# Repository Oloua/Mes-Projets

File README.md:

## Présentation

Bienvenue sur mon dépôt 👋

Ce repository regroupe l’ensemble de mes projets académiques, personnels et techniques dans les domaines de l’**intelligence artificielle**, des **systèmes embarqués**, de la **robotique**, de l’**IoT**, de la **vision par ordinateur** et du **développement logiciel**.

L’objectif de ce dépôt est de centraliser mes travaux, de suivre mon évolution en ingénierie et de constituer un **portfolio technique structuré** à destination des collaborateurs.

Les projets présents couvrent notamment :
- 🧠 **Intelligence artificielle / Machine Learning** : classification, apprentissage supervisé et non supervisé, analyse de données
- 🤖 **Robotique & systèmes embarqués** : contrôle de systèmes matériels, bras robotisé, intégration hardware/software
- 📡 **IoT (Internet of Things)** : capteurs, acquisition de données, communication sans fil, systèmes connectés
- 👁️ **Vision par ordinateur** : détection, reconnaissance faciale, traitement d’images
- ⚙️ **Développement logiciel & bas niveau** : Python, C/C++, Rust, MATLAB, OpenCV, TensorFlow
- 🔧 **Électronique & FPGA** : conception de systèmes numériques et prototypage matériel

Chaque dossier correspond à un projet indépendant (ex : *Projet IoT*, *Machine Learning*, *Voiture autonome en FreeRTOS*, *Identification faciale*, *Projet de fin d’études AI-in-Colibry-NPU*, *Stage 2025 Exosquelette*, etc.).

Certains fichiers volumineux (datasets, exécutables, environnements virtuels) sont exclus via `.gitignore` afin de garantir un dépôt propre et léger.

Ce dépôt évolue continuellement avec l’ajout de nouveaux projets et l’amélioration des projets existants.

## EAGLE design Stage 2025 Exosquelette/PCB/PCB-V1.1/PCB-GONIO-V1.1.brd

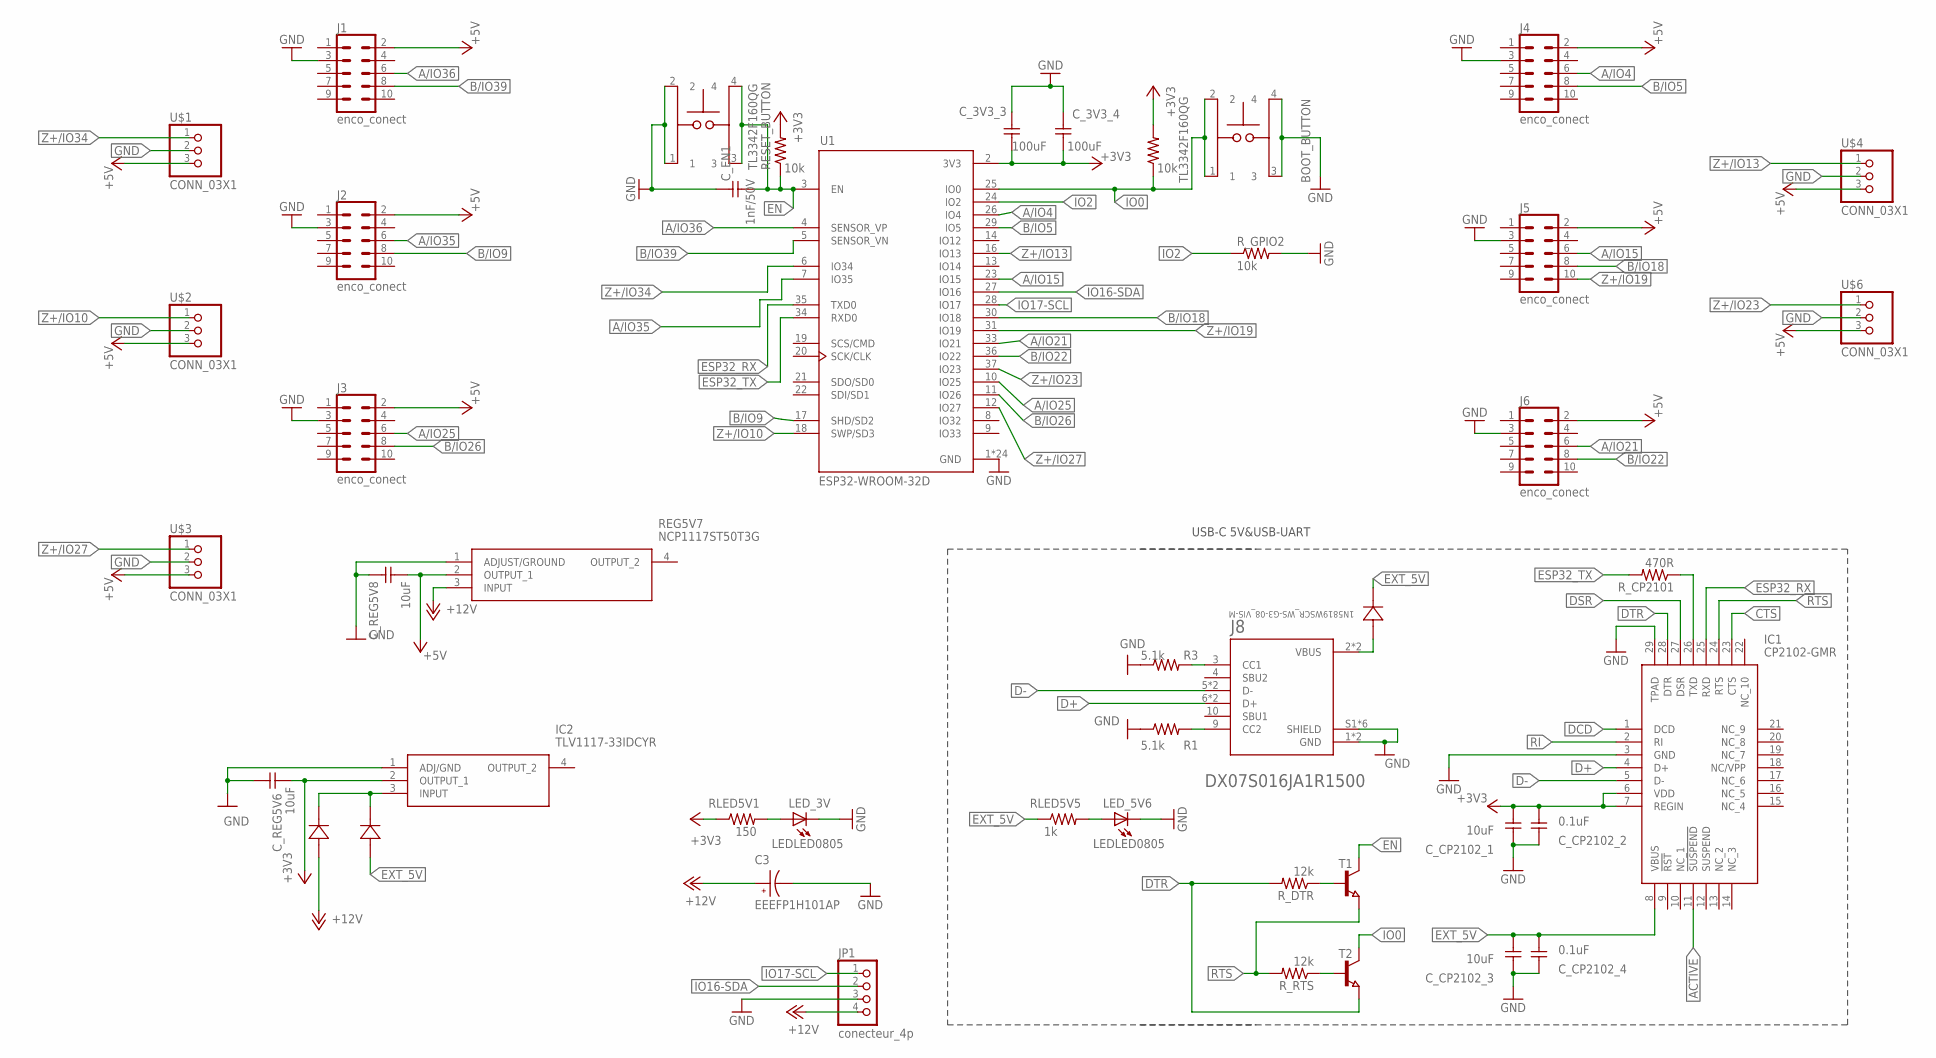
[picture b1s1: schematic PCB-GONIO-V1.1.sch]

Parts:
BOOT_BUTTON: TL3342F160QG; SW_TL3342F160QG
C3: EEEFP1H101AP; CAP_EEEFP1H101AP
CR1, CR2, CR3: 1N5819WSCR_WS-G3-08_VIS-M; CR_WS-G3-08_VIS-M
C_3V3_3, C_3V3_4: 100uF; C1206FAB
C_CP2102_1, C_CP2102_3: 10uF; C1206FAB
C_CP2102_2, C_CP2102_4: 0.1uF; C1206FAB
C_EN1: 1nF/50V; C1206FAB
C_REG5V6, C_REG5V8: 10uF; C1206FAB
IC1: CP2102-GMR; QFN50P500X500X100-29N
IC2: TLV1117-33IDCYR; SOT230P700X180-4N
J1, J2, J3, J4, J5, J6: enco_conect; 2X5-SHROUDED
J8: DX07S016JA1R1500; JAE_DX07S016JA1R1500
JP1: conecteur_4p; 1X04
LED_3V, LED_5V6: LEDLED0805; LEDC2012X90N
R1, R3: 5.1k; R1206W
REG5V7: NCP1117ST50T3G; SOT230P700X180-4N
RESET_BUTTON: TL3342F160QG; SW_TL3342F160QG
RLED5V1: 150; R1206FAB
RLED5V5: 1k; R1206FAB
R_CP2101: 470R; R1206FAB
R_DTR: 12k; R1206FAB
R_GPIO2: 10k; R1206FAB
R_PULL_UP1, R_PULL_UP3: 10k; R1206FAB
R_RTS: 12k; R1206FAB
T1, T2: T_NPN_S8050-J3Y_CHANGJ_SOT23-BEC; SOT23
U1: ESP32-WROOM-32D; MODULE_ESP32-WROOM-32D
U$1, U$2, U$3, U$4, U$6: CONN_03X1; 1X3

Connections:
+3V3: C_3V3_3.1, C_3V3_4.1, C_CP2102_1.1, C_CP2102_2.1, C_REG5V6.1, IC1.6 (VDD), IC1.7 (REGIN), IC2.2 (OUTPUT_1), RLED5V1.1, R_PULL_UP1.2, R_PULL_UP3.2, U1.2 (3V3)
+5V: C_REG5V8.1, J1.2, J2.2, J3.2, J4.2, J5.2, J6.2, REG5V7.2 (OUTPUT_1), U$1.3, U$2.3, U$3.3, U$4.3, U$6.3
+12V: C3.1, CR2.2, JP1.4, REG5V7.3 (INPUT)
A/IO4: J4.6, U1.26 (IO4)
A/IO15: J5.6, U1.23 (IO15)
A/IO21: J6.6, U1.33 (IO21)
A/IO25: J3.6, U1.10 (IO25)
A/IO35: J2.6, U1.7 (IO35)
A/IO36: J1.6, U1.4 (SENSOR_VP)
ACTIVE: IC1.11 (!SUSPEND)
B/IO5: J4.8, U1.29 (IO5)
B/IO9: J2.8, U1.17 (SHD/SD2)
B/IO18: J5.8, U1.30 (IO18)
B/IO22: J6.8, U1.36 (IO22)
B/IO26: J3.8, U1.11 (IO26)
B/IO39: J1.8, U1.5 (SENSOR_VN)
CTS: IC1.23 (CTS)
D+: IC1.4 (D+), J8.6 (D+), J8.7 (D+)
D-: IC1.5 (D-), J8.5 (D-), J8.8 (D-)
DCD: IC1.1 (DCD)
DSR: IC1.27 (DSR)
DTR: IC1.28 (DTR), R_DTR.2, T2.2 (E)
EN: C_EN1.1, RESET_BUTTON.3, RESET_BUTTON.4, R_PULL_UP1.1, T1.3 (C), U1.3 (EN)
ESP32_RX: IC1.25 (RXD), U1.35 (TXD0)
ESP32_TX: R_CP2101.2, U1.34 (RXD0)
EXT_5V: CR1.1, CR3.2, C_CP2102_3.1, C_CP2102_4.1, IC1.8 (VBUS), RLED5V5.1
GND: BOOT_BUTTON.3, BOOT_BUTTON.4, C3.2, C_3V3_3.2, C_3V3_4.2, C_CP2102_1.2, C_CP2102_2.2, C_CP2102_3.2, C_CP2102_4.2, C_EN1.2, C_REG5V6.2, C_REG5V8.2, IC1.3 (GND), IC1.29 (TPAD), IC2.1 (ADJ/GND), J1.3, J2.3, J3.3, J4.3, J5.3, J6.3, J8.1 (GND), J8.12 (GND), J8.S1 (SHIELD), J8.S2 (SHIELD), J8.S3 (SHIELD), J8.S4 (SHIELD), J8.S5 (SHIELD), J8.S6 (SHIELD), JP1.3, LED_3V.1 (C), LED_5V6.1 (C), R1.1, R3.1, REG5V7.1 (ADJUST/GROUND), RESET_BUTTON.1, RESET_BUTTON.2, R_GPIO2.2, U1.1 (GND), U1.15 (GND), U1.38 (GND), U1.39_1 (GND), U1.39_2 (GND), U1.39_3 (GND), U1.39_4 (GND), U1.39_5 (GND), U1.39_6 (GND), U1.39_7 (GND), U1.39_8 (GND), U1.39_9 (GND), U1.39_10 (GND), U1.39_11 (GND), U1.39_12 (GND), U1.39_13 (GND), U1.39_14 (GND), U1.39_15 (GND), U1.39_16 (GND), U1.39_17 (GND), U1.39_18 (GND), U1.39_19 (GND), U1.39_20 (GND), U1.39_21 (GND), U$1.2, U$2.2, U$3.2, U$4.2, U$6.2
GND1: J8.9 (CC2), R1.2
GND3: J8.3 (CC1), R3.2
IO0: BOOT_BUTTON.1, BOOT_BUTTON.2, R_PULL_UP3.1, T2.3 (C), U1.25 (IO0)
IO2: R_GPIO2.1, U1.24 (IO2)
IO16-SDA: JP1.2, U1.27 (IO16)
IO17-SCL: JP1.1, U1.28 (IO17)
unnamed: CR2.1, CR3.1, IC2.3 (INPUT)
unnamed: LED_3V.2 (A), RLED5V1.2
unnamed: CR1.2, J8.2 (VBUS), J8.11 (VBUS)
unnamed: IC1.26 (TXD), R_CP2101.1
unnamed: R_DTR.1, T1.1 (B)
unnamed: R_RTS.1, T2.1 (B)
unnamed: LED_5V6.2 (A), RLED5V5.2
RI: IC1.2 (RI)
RTS: IC1.24 (RTS), R_RTS.2, T1.2 (E)
Z+/IO10: U1.18 (SWP/SD3), U$2.1
Z+/IO13: U1.16 (IO13), U$4.1
Z+/IO19: J5.10, U1.31 (IO19)
Z+/IO23: U1.37 (IO23), U$6.1
Z+/IO27: U1.12 (IO27), U$3.1
Z+/IO34: U1.6 (IO34), U$1.1

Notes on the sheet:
USB-C 5V&USB-UART

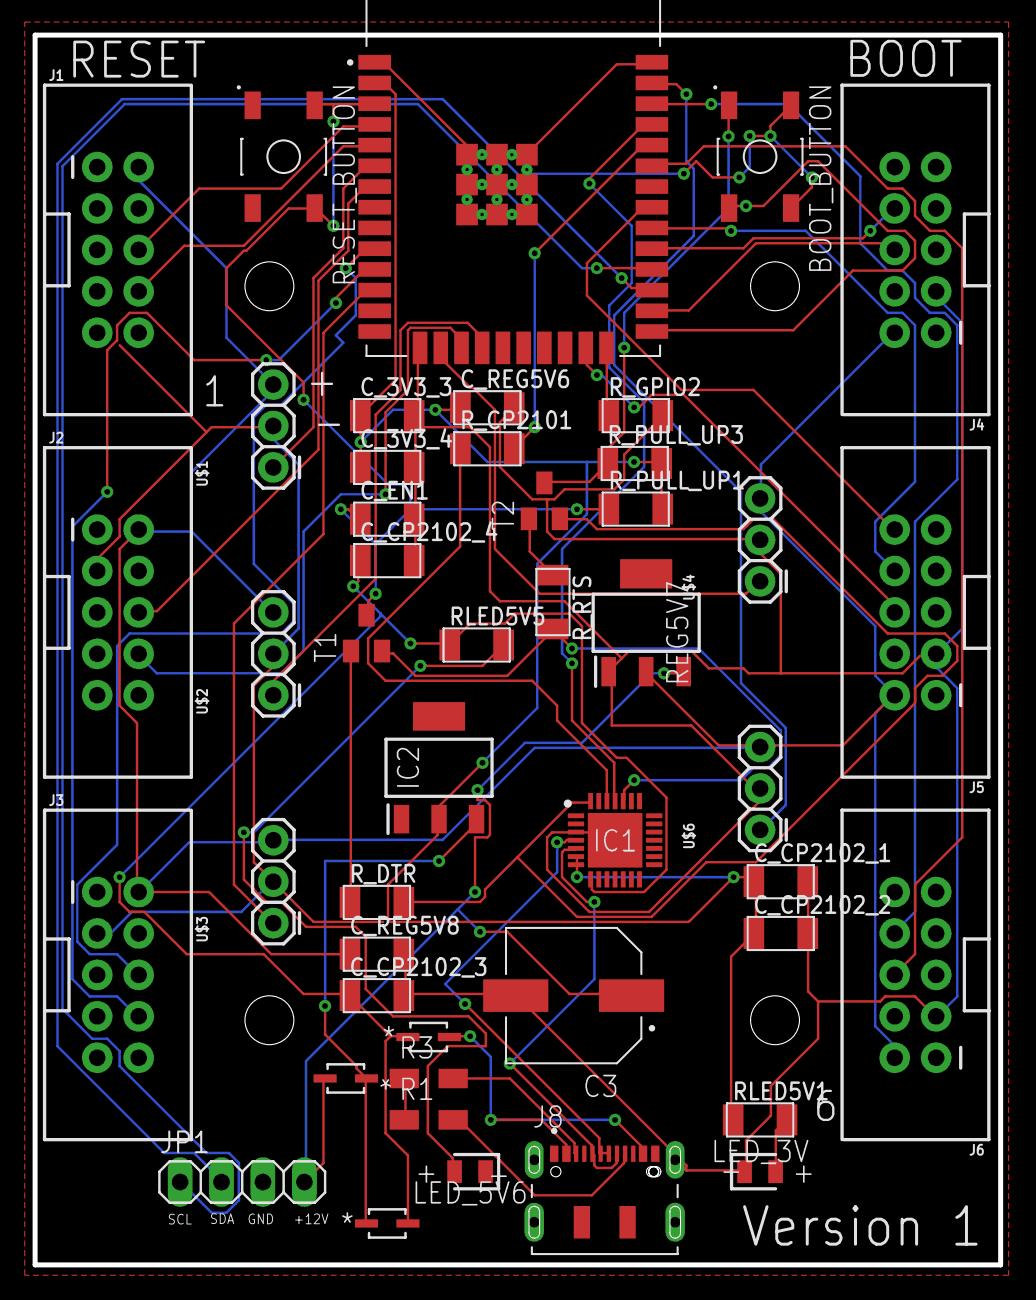
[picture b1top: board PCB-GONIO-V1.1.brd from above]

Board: 2 copper layers, 59.2 x 75.4 mm, 46 parts (0 on the bottom side), 43 nets.

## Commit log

2026-06-10 Premier envoi de tous mes projets
2026-06-10 Create README.md with project overview
    Added project descriptions in French and English.
2026-06-24 Create Stage 2026 : Contrôle d’un outil Milwaukee à l’aide d’un bras UR20

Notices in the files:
parts and their libraries:
COPYRIGHT: Copyright (C) 2022 Ultra Librarian. All rights reserved.
